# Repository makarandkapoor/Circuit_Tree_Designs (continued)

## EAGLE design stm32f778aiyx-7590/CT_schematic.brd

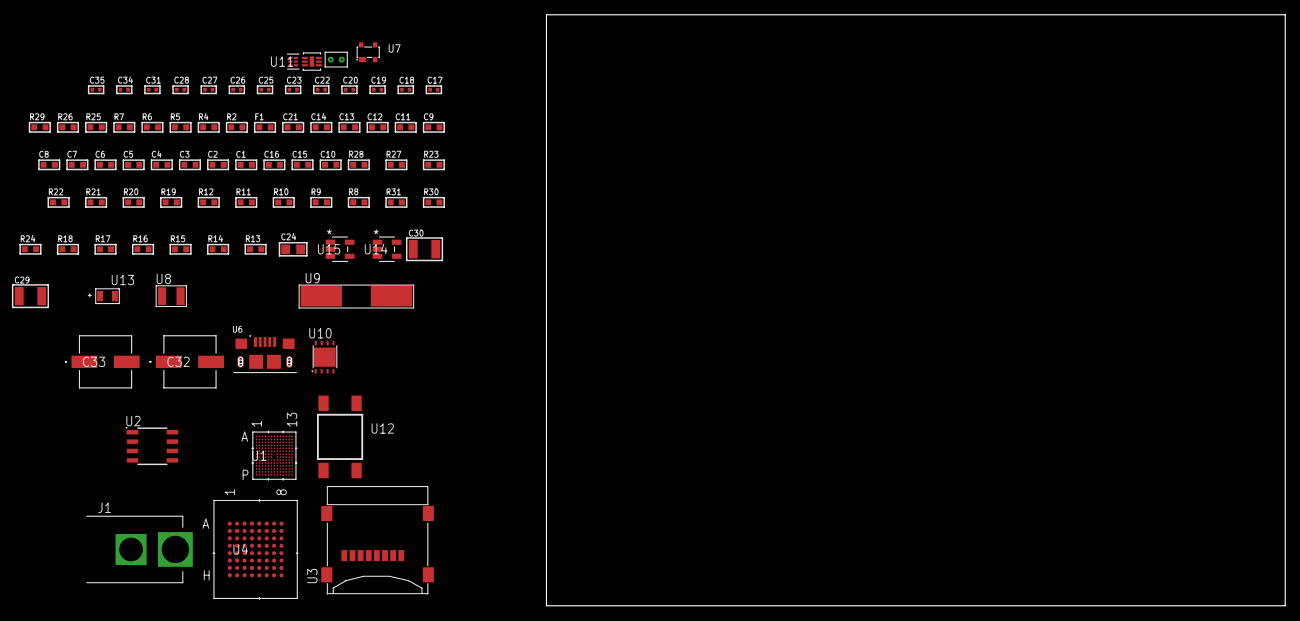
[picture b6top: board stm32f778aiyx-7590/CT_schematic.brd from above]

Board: 2 copper layers, 82 parts (0 on the bottom side), 86 nets, no tracks yet.

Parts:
C1, C13, C21: 1e-06; C0603
C2, C3, C4, C5, C6, C7, C8, C9, C11, C14: 1e-07; C0603
C10: 4.7e-06; C0603
C12: 1e-08; C0603
C15, C16: 2.2e-06; C0603
C17, C18, C19, C20: 1e-11; C0402
C22, C25, C26, C28, C34, C35: 1e-08; C0402
C23, C27, C31: 1e-07; C0402
C24: 1e-05; C0805
C29, C30: 1e-05; C1210
C32, C33: 0.0001; EXV-9H
F1: 240.0; L0603
J1: PJ-037B; PJ-037B_PACKAGE
R2, R26: 1000.0; R0603
R4, R5: 4700.0; R0603
R6, R7: 2200.0; R0603
R8, R9, R10, R11, R12, R19, R20, R21, R22, R23, R27, R28: 10000.0; R0603
R13, R14, R15, R16, R17, R18, R24: 100000.0; R0603
R25: 2231.0; R0603
R29: 9100.0; R0603
R30: 680000.0; R0603
R31: 120000.0; R0603
U1: STM32F778AIY6TR; WLCSP180
U2: AT25128B-SSHL-T; SOIC-8
U3: 0472192001; MOLEX_47219-2001
U4: mt28ew256aba1HPC-0SIT; LBGA-64
U5: SI7006-A20-IM; DFN-6
U6: 10118193-0001LF; FCI_10118193-0001LF
U7: prtr5v0u2ax; SOT143B
U8: ABS07-32.768KHZ-7-T
U9: ABLS-25.000MHZ-B2F-T
U10: LP3878SDX-ADJ/NOPB; WSON-8
U11: TPS3895ADRYR; SON-6
U12: 4-1437565-2; SW_4-1437565-2
U13: Q65110A2395; LGM67K-G1J2-24-Z
U14, U15: nc7sz125m5x; NC7SZ125M5X
U16: Dummy; DUMMY_PACKAGE_192

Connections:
CLK_CRYSTAL_U1_E12: C17.1, U1.E12, U8.1
CLK_CRYSTAL_U1_E13: C18.1, U1.E13, U8.2
CLK_CRYSTAL_U1_K12: C19.1, U1.K12, U9.1
CLK_CRYSTAL_U1_K13: C20.1, U1.K13, U9.2
GND: C1.2, C2.2, C3.2, C4.2, C5.2, C6.2, C7.2, C8.2, C9.2, C10.2, C11.2, C12.2, C13.2, C14.2, C15.2, C16.2, C17.2, C18.2, C19.2, C20.2, C21.2, C22.2, C23.2, C24.2, C25.2, C26.2, C27.2, C28.2, C29.2, C30.2, C31.2, C32.2, C33.2, C34.2, C35.2, J1.2, R2.2, R8.2, R26.2, R29.2, R31.2, U1.A8, U1.A11, U1.B6, U1.C2, U1.E3, U1.F1, U1.F13, U1.H5, U1.J9, U1.J13, U1.M1, U1.M11, U1.N4, U1.N5, U1.P9, U2.4, U3.6, U3.G1, U3.G2, U3.G3, U3.G4, U4.E8, U4.H2, U4.H7, U5.2, U5.7, U6.5, U6.6, U6.7, U6.8, U6.9, U7.1, U10.3, U10.PAD, U11.2, U13.C, U14.1, U14.3, U15.1, U15.3, U16.1
NET_U1_A10: R8.1, U1.A10
NET_U1_B9: R6.1, U1.B9, U5.6
NET_U1_C1: C16.1, U1.C1
NET_U1_C8: R7.1, U1.C8, U5.1
NET_U1_C10: R9.1, U1.C10
NET_U1_L11: R5.1, U1.L11, U15.4
NET_U1_M12: C12.1, C13.1, F1.1, U1.M12
NET_U1_P5: C15.1, U1.P5
NET_U1_P11: U12.3, U12.4
NET_U2_3: R10.1, U2.3
NET_U2_7: R12.1, U2.7
NET_U4_B4: R22.1, U4.B4
NET_U4_B5: R4.1, U4.B5, U14.4
NET_U10_1: C28.1, U10.1
NET_U10_6: R25.2, R26.1, U10.6
NET_U10_8: R24.1, U10.8
NET_U11_1: R28.1, R29.1, U11.1
NET_U11_3: R30.2, R31.1, U11.3
NET_U11_4: R27.1, U11.4, U14.2, U15.2
NET_U12_1: R2.1, U12.1, U12.2
PROC_DAC_OUT1: U1.L9, U16.2
PROC_FMC_A0: U1.G11, U4.E2
PROC_FMC_A1: U1.G12, U4.D2
PROC_FMC_A2: U1.G13, U4.C2
PROC_FMC_A3: U1.H11, U4.A2
PROC_FMC_A4: U1.H12, U4.B2
PROC_FMC_A5: U1.H13, U4.D3
PROC_FMC_A6: U1.K7, U4.C3
PROC_FMC_A7: U1.L8, U4.A3
PROC_FMC_A8: U1.K8, U4.B6
PROC_FMC_A9: U1.P8, U4.A6
PROC_FMC_A10: U1.N8, U4.C6
PROC_FMC_A11: U1.L7, U4.D6
PROC_FMC_A12: U1.H9, U4.B7
PROC_FMC_A13: U1.G9, U4.A7
PROC_FMC_A14: U1.G1, U4.C7
PROC_FMC_A15: U1.G2, U4.D7
PROC_FMC_A16: U1.K3, U4.E7
PROC_FMC_A17: U1.J4, U4.B3
PROC_FMC_A18: U1.L2, U4.C4
PROC_FMC_A19: U1.F10, U4.D5
PROC_FMC_A20: U1.C12, U4.D4
PROC_FMC_A21: U1.D12, U4.C5
PROC_FMC_A22: U1.E11, U4.B8
PROC_FMC_A23: U1.E10, U4.C8
PROC_FMC_D0: U1.L1, U4.E3
PROC_FMC_D1: U1.K2, U4.H3
PROC_FMC_D2: U1.A4, U4.E4
PROC_FMC_D3: U1.D5, U4.H4
PROC_FMC_D4: U1.M7, U4.H5
PROC_FMC_D5: U1.N7, U4.E5
PROC_FMC_D6: U1.P7, U4.H6
PROC_FMC_D7: U1.J6, U4.E6
PROC_FMC_D8: U1.K6, U4.F3
PROC_FMC_D9: U1.L6, U4.G3
PROC_FMC_D10: U1.P6, U4.F4
PROC_FMC_D11: U1.N6, U4.G4
PROC_FMC_D12: U1.M6, U4.F5
PROC_FMC_D13: U1.M3, U4.G6
PROC_FMC_D14: U1.L3, U4.F6
PROC_FMC_D15: U1.M2, U4.G7
PROC_FMC_NBL0: R23.1, U1.C9, U4.F7
PROC_FMC_NE2: R19.1, U1.D7, U4.F2
PROC_FMC_NOE: R20.1, U1.A5, U4.G2
PROC_FMC_NWAIT: U1.E6, U4.A4
PROC_FMC_NWE: R21.1, U1.C5, U4.A5
PROC_SDMMC1_CK: R14.1, U1.D4, U3.5
PROC_SDMMC1_CMD: R13.1, U1.D6, U3.3
PROC_SDMMC1_D0: R15.1, U1.G8, U3.7
PROC_SDMMC1_D1: R16.1, U1.E1, U3.8
PROC_SDMMC1_D2: R17.1, U1.B4, U3.1
PROC_SDMMC1_D3: R18.1, U1.C4, U3.2
PROC_SPI1_MISO: U1.C6, U2.2
PROC_SPI1_MOSI: U1.A9, U2.5
PROC_SPI1_NSS: R11.1, U1.A7, U2.1
PROC_SPI1_SCK: U1.B7, U2.6
PROC_USB_OTG_FS_DM: U1.E3, U6.2, U7.3
PROC_USB_OTG_FS_DP: U1.D1, U6.3, U7.2
PROC_USB_OTG_FS_VBUS: C21.1, U1.F4, U6.1, U7.4
VCC_S1_11V4: C29.1, C32.1, C33.1, J1.1, R24.2, U10.4
VCC_TIER1_3V3: C1.1, C2.1, C3.1, C4.1, C5.1, C6.1, C7.1, C8.1, C9.1, C10.1, C11.1, C14.1, C22.1, C23.1, C24.1, C25.1, C26.1, C27.1, C30.1, C31.1, C34.1, C35.1, F1.2, R4.2, R5.2, R6.2, R7.2, R9.2, R10.2, R11.2, R12.2, R13.2, R14.2, R15.2, R16.2, R17.2, R18.2, R19.2, R20.2, R21.2, R22.2, R23.2, R25.1, R27.2, R28.2, R30.1, U1.A6, U1.B2, U1.B8, U1.B11, U1.C13, U1.F2, U1.F12, U1.J12, U1.K1, U1.K9, U1.M8, U1.P4, U2.8, U3.4, U4.D8, U4.F1, U4.G5, U5.5, U10.5, U11.6, U14.5, U15.5

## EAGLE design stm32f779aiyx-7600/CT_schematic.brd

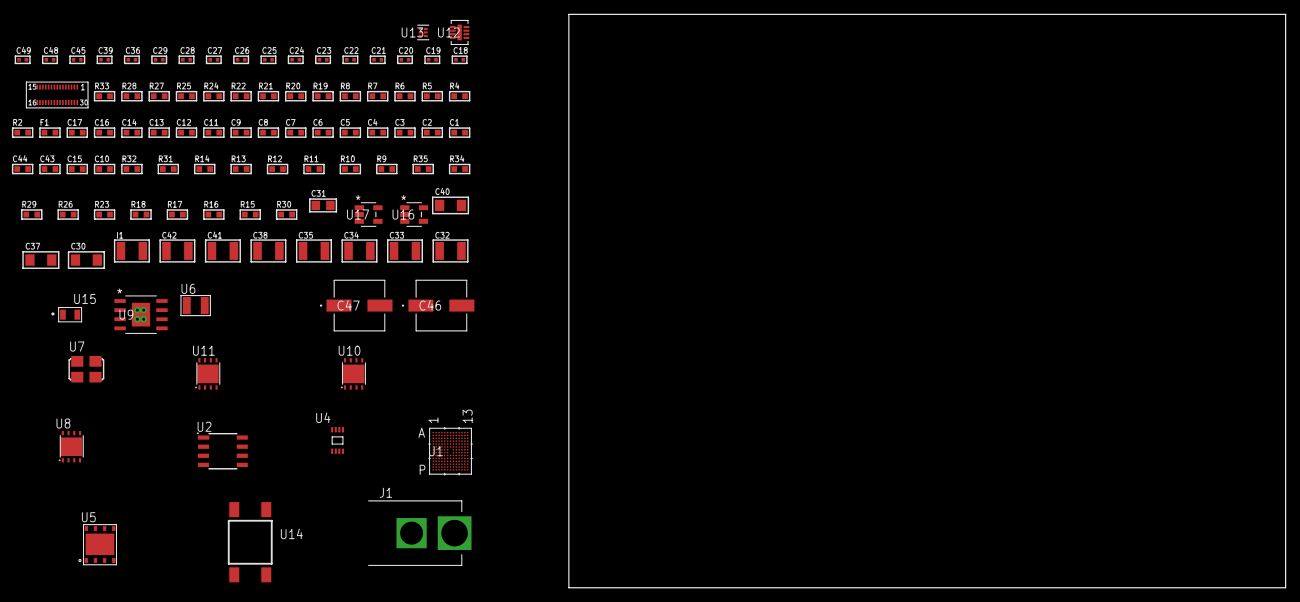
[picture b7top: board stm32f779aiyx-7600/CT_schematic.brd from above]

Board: 2 copper layers, 100.0 x 80.0 mm, 102 parts (0 on the bottom side), 57 nets, no tracks yet.

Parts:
C1, C13: 1e-06; C0603
C2, C3, C4, C5, C6, C7, C8, C9, C11, C14, C16, C17: 1e-07; C0603
C10: 4.7e-06; C0603
C12: 1e-08; C0603
C15, C43: 2.2e-06; C0603
C18, C19: 1e-11; C0402
C20, C26, C28, C29, C36, C39, C48, C49: 1e-08; C0402
C21, C22, C23, C24, C25, C27, C45: 1e-07; C0402
C30, C37, C40: 1e-05; C1206
C31: 1e-05; C0805
C32, C33, C34, C35, C38, C41, C42: 1e-05; C1210
C44: 2.2e-07; C0603
C46, C47: 0.0001; EXV-9H
F1: 240.0; L0603
I1: 1e-05; L1210
J1: PJ-037B; PJ-037B_PACKAGE
R2, R20, R25, R28: 1000.0; R0603
R4, R5: 4700.0; R0603
R6, R7, R8, R22: 2200.0; R0603
R9, R10, R11, R12, R13, R14, R31, R32: 10000.0; R0603
R15, R16, R17, R18, R23, R26, R29: 100000.0; R0603
R19: 200.0; R0603
R21: 910.0; R0603
R24: 1800.0; R0603
R27: 2231.0; R0603
R30: 1600000.0; R0603
R33: 9100.0; R0603
R34: 680000.0; R0603
R35: 120000.0; R0603
U1: STM32F779AIY6TR; WLCSP180
U2: AT25160B-SSHL-T; SOIC-8
U3: LH430WV2-SD01
U4: 24AA02T-I/MNY; TDFN-8/6MM
U5: SST26VF032B-104I/MF; WFDN-8
U6: ABS07-32.768KHZ-7-T
U7: ASFL1-25MHZ-NCS; ASFL1
U8, U10, U11: LP3878SDX-ADJ/NOPB; WSON-8
U9: MIC5234YME; SOIC-8_EP
U12: LT3494AEDDB#TRMPBF; DFN-8_DDB
U13: TPS3895ADRYR; SON-6
U14: 4-1437565-2; SW_4-1437565-2
U15: Q65110A2395; LGM67K-G1J2-24-Z
U16, U17: nc7sz125m5x; NC7SZ125M5X

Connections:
CLK_CRYSTAL_U1_E12: C18.1, U1.E12, U6.1
CLK_CRYSTAL_U1_E13: C19.1, U1.E13, U6.2
CLK_U1_K12: U1.K12, U7.3
GND: C1.2, C2.2, C3.2, C4.2, C5.2, C6.2, C7.2, C8.2, C9.2, C10.2, C11.2, C12.2, C13.2, C14.2, C15.2, C16.2, C17.2, C18.2, C19.2, C20.2, C21.2, C22.2, C23.2, C24.2, C25.2, C26.2, C27.2, C28.2, C29.2, C30.2, C31.2, C32.2, C33.2, C34.2, C35.2, C36.2, C37.2, C38.2, C39.2, C40.2, C41.2, C42.2, C43.2, C44.2, C45.2, C46.2, C47.2, C48.2, C49.2, J1.2, R2.2, R9.2, R14.2, R20.2, R22.2, R25.2, R28.2, R33.2, R35.2, U1.A8, U1.A11, U1.B6, U1.C2, U1.F1, U1.F13, U1.H5, U1.J9, U1.J13, U1.M1, U1.M11, U1.N4, U1.N5, U1.P9, U2.4, U3.1, U3.6, U3.9, U3.12, U3.15, U3.17, U3.18, U3.19, U3.24, U3.27, U4.4, U4.7, U5.4, U5.9, U7.2, U8.3, U8.PAD, U9.7, U9.EPAD, U10.3, U10.PAD, U11.3, U11.PAD, U12.2, U12.9, U13.2, U15.C, U16.1, U16.3, U17.1, U17.3
NET_U1_A10: R9.1, U1.A10
NET_U1_B9: R6.1, U1.B9, U4.6
NET_U1_C1: C17.1, U1.C1
NET_U1_C8: R7.1, U1.C8, U4.5
NET_U1_C10: R10.1, U1.C10
NET_U1_J3: C15.1, U1.H6, U1.J3
NET_U1_L11: R5.1, U1.L11, U17.4
NET_U1_M12: C12.1, C13.1, F1.1, U1.M12
NET_U1_P11: U14.3, U14.4
NET_U2_3: R11.1, U2.3
NET_U2_7: R13.1, U2.7
NET_U3_4: R4.1, U3.4, U16.4
NET_U3_20: R14.1, U3.20
NET_U8_1: C29.1, U8.1
NET_U8_6: R19.2, R20.1, U8.6
NET_U8_8: R18.1, U8.8
NET_U9_4: R21.2, R22.1, U9.4
NET_U10_1: C36.1, U10.1
NET_U10_6: R24.2, R25.1, U10.6
NET_U10_8: R23.1, U10.8
NET_U11_1: C39.1, U11.1
NET_U11_6: R27.2, R28.1, U11.6
NET_U11_8: R26.1, U11.8
NET_U12_1: I1.1, U12.1
NET_U12_5: R29.1, U12.5
NET_U12_6: R30.1, U12.6
NET_U12_8: C44.1, U12.8
NET_U13_1: R32.1, R33.1, U13.1
NET_U13_3: R34.2, R35.1, U13.3
NET_U13_4: R31.1, U13.4, U16.2, U17.2
NET_U14_1: R2.1, U14.1, U14.2
PROC_DSIHOST_CKN: U1.H3, U3.13
PROC_DSIHOST_CKP: U1.H4, U3.14
PROC_DSIHOST_D0N: U1.J2, U3.7
PROC_DSIHOST_D0P: U1.J1, U3.8
PROC_DSIHOST_D1N: U1.H2, U3.10
PROC_DSIHOST_D1P: U1.H1, U3.11
PROC_QUADSPI_BK1_IO0: U1.E1, U5.5
PROC_QUADSPI_BK1_IO1: U1.B4, U5.2
PROC_QUADSPI_BK1_IO2: R16.1, U1.E10, U5.3
PROC_QUADSPI_BK1_IO3: R17.1, U1.J11, U5.7
PROC_QUADSPI_BK1_NCS: R15.1, U1.K5, U5.1
PROC_QUADSPI_CLK: U1.J7, U5.6
PROC_SPI1_MISO: U1.C6, U2.2
PROC_SPI1_MOSI: U1.A9, U2.5
PROC_SPI1_NSS: R12.1, U1.A7, U2.1
PROC_SPI1_SCK: U1.B7, U2.6
VCC_S1_10V6: C30.1, C32.1, C33.1, C37.1, C40.1, C42.1, C46.1, C47.1, I1.2, J1.1, R18.2, R23.2, R26.2, R29.2, U8.4, U9.5, U9.8, U10.4, U11.4, U12.3, U12.4
VCC_TIER1_1V2: C16.1, C31.1, R19.1, U1.P5, U8.5
VCC_TIER1_1V5: C34.1, C35.1, R21.1, U3.29, U9.1
VCC_TIER1_2V8: C23.1, C24.1, C25.1, C38.1, R24.1, U3.16, U3.21, U3.22, U3.23, U10.5
VCC_TIER1_3V3: C1.1, C2.1, C3.1, C4.1, C5.1, C6.1, C7.1, C8.1, C9.1, C10.1, C11.1, C14.1, C20.1, C21.1, C26.1, C27.1, C28.1, C41.1, C45.1, C48.1, C49.1, F1.2, R4.2, R5.2, R6.2, R7.2, R8.2, R10.2, R11.2, R12.2, R13.2, R15.2, R16.2, R17.2, R27.1, R31.2, R32.2, R34.1, U1.A6, U1.B2, U1.B8, U1.B11, U1.C13, U1.F2, U1.F12, U1.J12, U1.K1, U1.K9, U1.M8, U1.P4, U2.8, U3.2, U4.8, U5.8, U7.4, U11.5, U13.6, U16.5, U17.5
VCC_TIER1_12V0: C22.1, C43.1, R30.2, U3.30, U12.7

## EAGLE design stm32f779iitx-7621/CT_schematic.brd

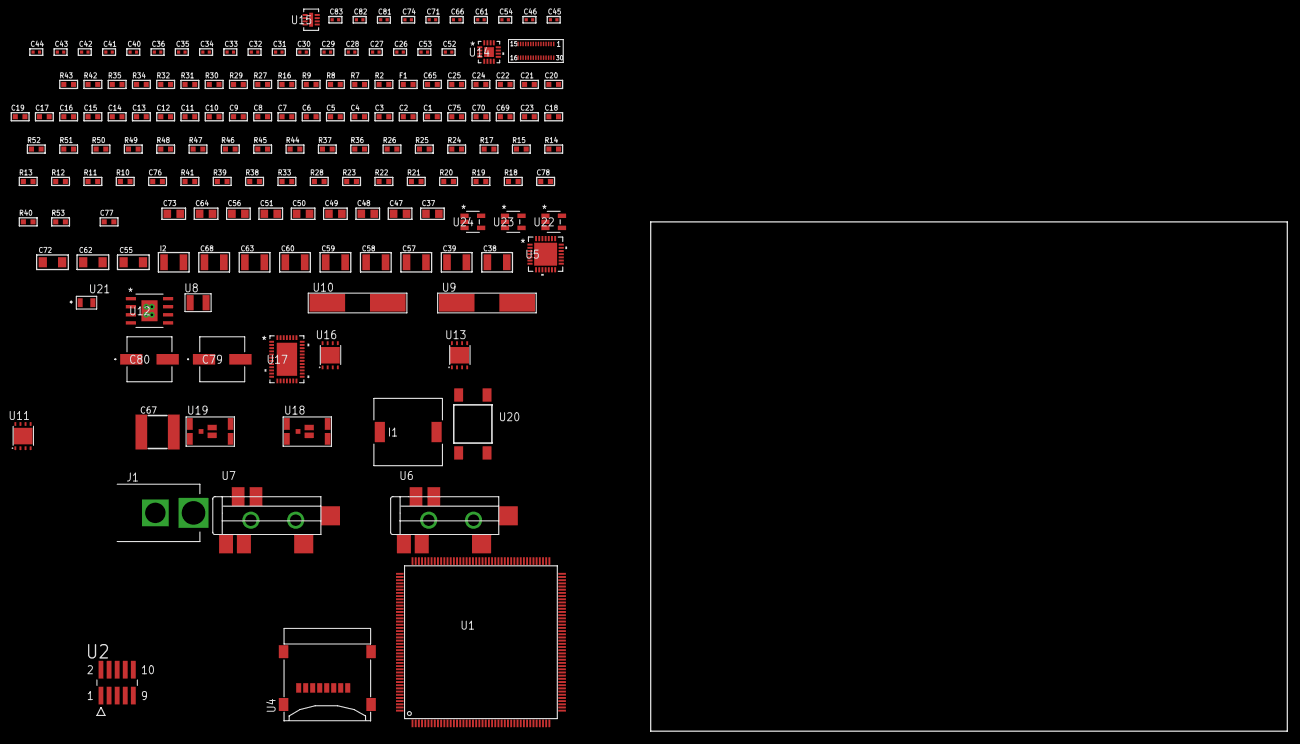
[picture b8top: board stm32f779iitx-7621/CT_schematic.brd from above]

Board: 2 copper layers, 100.0 x 80.0 mm, 159 parts (0 on the bottom side), 85 nets, no tracks yet.

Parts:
C1, C21, C65: 1e-06; C0603
C2, C3, C4, C5, C6, C7, C8, C9, C10, C11, C12, C13, C14, C15, C16, C17, C19, C22, C24, C25: 1e-07; C0603
C18: 4.7e-06; C0603
C20: 1e-08; C0603
C23, C69, C75: 2.2e-06; C0603
C26, C27, C28, C29: 1e-11; C0402
C30, C31, C32, C33, C34, C35, C36, C42, C43, C44, C45, C46, C66, C74: 1e-07; C0402
C37, C47, C48, C49, C50, C51, C56, C64, C73: 1e-05; C0805
C38, C39: 2.2e-05; C1210
C40, C41: 1e-09; C0402
C52, C53: 2.2e-11; C0402
C54, C61, C71, C81, C82, C83: 1e-08; C0402
C55, C62, C72: 1e-05; C1206
C57, C58, C59, C60, C63, C68: 1e-05; C1210
C67: 6.8e-05; 2220
C70: 2.2e-07; C0603
C76: 2.45e-08; R0603
C77: 2.8258362168397e-09; R0603
C78: 7.105e-09; R0603
C79, C80: 0.0001; EXV-9H
F1: 240.0; L0603
I1: 5.2e-06; DR1040
I2: 1e-05; L1210
J1: PJ-037B; PJ-037B_PACKAGE
R2, R30, R35, R43: 1000.0; R0603
R7, R8: 4700.0; R0603
R9, R32: 2200.0; R0603
R10, R11, R12, R13, R14, R15, R17, R44, R46, R47, R50, R51, R52: 10000.0; R0603
R16: 5.0; R0603
R18, R19, R20, R21, R22, R23, R28, R33, R39, R41: 100000.0; R0603
R24, R25, R26: 47000.0; R0603
R27: 680.0; R0603
R29, R42: 200.0; R0603
R31: 910.0; R0603
R34: 1800.0; R0603
R36: 20000.0; R0603
R37: 91000.0; R0603
R38: 300000.0; R0603
R40: 1600000.0; R0603
R45: 75000.0; R0603
R48, R49: 95300.0; R0603
R53: 83745.454545455; R0603
U1: STM32F779IIT6; LQFP176
U2: FTSH-105-01-L-DV-K; SAMTEC_FTSH-105-01-L-DV-K
U3: LH430WV2-SD01
U4: 0472192001; MOLEX_47219-2001
U5: WM8731CLSEFL; QFN-28
U6, U7: SJ-43515TS-SMT-TR
U8: ABS07-32.768KHZ-7-T
U9: ABLS-25.000MHZ-B2F-T
U10: ABLS-12.288MHZ-B4-T
U11, U13, U16: LP3878SDX-ADJ/NOPB; WSON-8
U12: MIC5234YME; SOIC-8_EP
U14: LTC3601EUD#PBF; QFN-16_EP
U15: LT3494AEDDB#TRMPBF; DFN-8_DDB
U17: LTC2928CUHF#PBF; QFN-38_UHF
U18, U19: IRF8306MTRPbF; IRF8306MTRPBF
U20: 4-1437565-2; SW_4-1437565-2
U21: Q65110A2395; LGM67K-G1J2-24-Z
U22, U23, U24: nc7sz125m5x; NC7SZ125M5X

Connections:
CLK_CRYSTAL_U1_9: C26.1, U1.9, U8.1
CLK_CRYSTAL_U1_10: C27.1, U1.10, U8.2
CLK_CRYSTAL_U1_29: C28.1, U1.29, U9.1
CLK_CRYSTAL_U1_30: C29.1, U1.30, U9.2
CLK_CRYSTAL_U5_1: C52.1, U5.1, U10.1
CLK_CRYSTAL_U5_2: C53.1, U5.2, U10.2
GND: C1.2, C2.2, C3.2, C4.2, C5.2, C6.2, C7.2, C8.2, C9.2, C10.2, C11.2, C12.2, C13.2, C14.2, C15.2, C16.2, C17.2, C18.2, C19.2, C20.2, C21.2, C22.2, C23.2, C24.2, C25.2, C26.2, C27.2, C28.2, C29.2, C30.2, C31.2, C32.2, C33.2, C34.2, C35.2, C36.2, C37.2, C41.2, C42.2, C43.2, C44.2, C45.2, C46.2, C47.2, C48.2, C49.2, C50.2, C51.2, C52.2, C53.2, C54.2, C55.2, C56.2, C57.2, C58.2, C59.2, C60.2, C61.2, C62.2, C63.2, C64.2, C65.2, C67.1, C67.2, C68.2, C69.2, C70.2, C71.2, C72.2, C73.2, C74.2, C75.2, C76.2, C77.2, C78.2, C79.2, C80.2, C81.2, C82.2, C83.2, J1.2, R2.2, R10.2, R16.2, R17.2, R24.2, R25.2, R26.2, R30.2, R32.2, R35.2, R36.2, R38.2, R43.2, R45.2, R48.2, R49.2, R50.2, R51.2, R52.2, U1.14, U1.22, U1.37, U1.61, U1.71, U1.95, U1.103, U1.109, U1.117, U1.130, U1.135, U1.148, U1.158, U2.3, U2.5, U3.1, U3.6, U3.9, U3.12, U3.15, U3.17, U3.18, U3.19, U3.24, U3.27, U4.6, U4.G1, U4.G2, U4.G3, U4.G4, U5.4, U5.15, U5.19, U5.25, U5.26, U5.29, U6.1, U7.1, U11.3, U11.PAD, U12.7, U12.EPAD, U13.3, U13.PAD, U14.1, U14.9, U14.17, U15.2, U15.9, U16.3, U16.PAD, U17.8, U17.9, U17.10, U17.12, U17.13, U17.24, U17.25, U17.30, U17.32, U17.39, U21.C, U22.2, U22.3, U23.1, U23.3, U24.1, U24.3
NET_U1_31: R8.1, U1.31, U24.4
NET_U1_39: C20.1, C21.1, F1.1, U1.38, U1.39
NET_U1_48: R12.1, U1.48
NET_U1_106: C23.1, U1.100, U1.106
NET_U1_129: C25.1, U1.129
NET_U1_166: R10.1, U1.166
NET_U1_171: R11.1, U1.171
NET_U1_176: U20.3, U20.4
NET_U2_9: R16.1, U2.9
NET_U3_4: R7.1, U3.4, U23.4
NET_U3_20: R17.1, U3.20
NET_U5_20: C46.1, C51.1, U5.20
NET_U6_2: C39.1, R25.1, U6.2
NET_U6_5: C38.1, R24.1, U6.5
NET_U7_5: C40.1, C41.1, R26.1, R27.1, U7.5
NET_U11_1: C54.1, U11.1
NET_U11_6: R29.2, R30.1, U11.6
NET_U11_8: R28.1, U11.8
NET_U12_4: R31.2, R32.1, U12.4
NET_U13_1: C61.1, U13.1
NET_U13_6: R34.2, R35.1, U13.6
NET_U13_8: R33.1, U13.8
NET_U14_3: C66.2, I1.1, U14.3, U14.4
NET_U14_6: C66.1, U14.6
NET_U14_7: C65.1, U14.7, U14.12
NET_U14_10: R38.1, U14.10
NET_U14_11: R36.1, R37.1, U14.11
NET_U14_ATNET_3: I1.2, R37.2
NET_U15_1: I2.1, U15.1
NET_U15_5: R39.1, U15.5
NET_U15_6: R40.1, U15.6
NET_U15_8: C70.1, U15.8
NET_U16_1: C71.1, U16.1
NET_U16_6: R42.2, R43.1, U16.6
NET_U16_8: R41.1, U16.8
NET_U17_3: R51.1, U17.3
NET_U17_6: R48.1, U17.6
NET_U17_7: R49.1, U17.7
NET_U17_16: R50.1, R53.1, U17.16
NET_U17_18: R47.1, U17.18
NET_U17_19: R46.1, U17.19, U17.20
NET_U17_21: R44.1, R45.1, U17.21, U22.4, U23.2, U24.2
NET_U17_22: C74.1, R44.2, R46.2, R47.2, U17.11, U17.22
NET_U17_26: C77.1, U17.26
NET_U17_27: C76.1, U17.27
NET_U17_28: C78.1, U17.28
NET_U17_38: R52.1, U17.38
NET_U18_3: U17.2, U18.3
NET_U19_3: U17.37, U19.3
NET_U20_1: R2.1, U20.1, U20.2
PROC_DSIHOST_CKN: U1.105, U3.13
PROC_DSIHOST_CKP: U1.104, U3.14
PROC_DSIHOST_D0N: U1.102, U3.7
PROC_DSIHOST_D0P: U1.101, U3.8
PROC_DSIHOST_D1N: U1.108, U3.10
PROC_DSIHOST_D1P: U1.107, U3.11
PROC_I2S1_CK: U1.51, U5.7
PROC_I2S1_SD: U1.53, U5.8
PROC_I2S1_WS: U1.50, U5.9, U5.11
PROC_SDMMC1_CK: R19.1, U1.141, U4.5
PROC_SDMMC1_CMD: R18.1, U1.144, U4.3
PROC_SDMMC1_D0: R20.1, U1.121, U4.7
PROC_SDMMC1_D1: R21.1, U1.122, U4.8
PROC_SDMMC1_D2: R22.1, U1.139, U4.1
PROC_SDMMC1_D3: R23.1, U1.140, U4.2
PROC_SYS_JTCK_SWCLK: R14.1, U1.137, U2.4
PROC_SYS_JTDO_SWO: U1.161, U2.6
PROC_SYS_JTMS_SWDIO: R15.1, U1.128, U2.2
RST_OUT_U2_JTAG_RST_B: R13.1, U2.10, U22.1
VCC_10V5: C75.1, C79.1, C80.1, J1.1, R53.2, U17.23, U18.1, U18.2, U18.6, U18.7, U19.1, U19.2, U19.6, U19.7
VCC_S1_10V5: C55.1, C57.1, C58.1, C62.1, C64.1, C68.1, I2.2, R28.2, R33.2, R39.2, U11.4, U12.5, U12.8, U13.4, U14.15, U14.16, U15.3, U15.4, U18.4, U18.5
VCC_S2_10V5: C72.1, R41.2, U16.4, U19.4, U19.5
VCC_TIER1_1V2: C24.1, C56.1, R29.1, U1.81, U11.5
VCC_TIER1_1V5: C59.1, C60.1, R31.1, U3.29, U12.1
VCC_TIER1_2V8: C33.1, C34.1, C35.1, C63.1, R34.1, U3.16, U3.21, U3.22, U3.23, U13.5
VCC_TIER1_3V3: C1.1, C2.1, C3.1, C4.1, C5.1, C6.1, C7.1, C8.1, C9.1, C10.1, C11.1, C12.1, C13.1, C14.1, C15.1, C16.1, C17.1, C18.1, C19.1, C22.1, C30.1, C31.1, C36.1, C37.1, C42.1, C43.1, C44.1, C45.1, C47.1, C48.1, C49.1, C50.1, C67.2, C81.1, C82.1, C83.1, F1.2, I1.2, R7.2, R8.2, R9.2, R11.2, R12.2, R13.2, R14.2, R15.2, R18.2, R19.2, R20.2, R21.2, R22.2, R23.2, R37.2, U1.6, U1.15, U1.23, U1.36, U1.49, U1.62, U1.72, U1.82, U1.96, U1.99, U1.118, U1.131, U1.136, U1.149, U1.159, U1.172, U2.1, U3.2, U4.4, U5.3, U5.5, U5.12, U5.18, U14.8, U22.5, U23.5, U24.5
VCC_TIER1_12V0: C32.1, C69.1, R40.2, U3.30, U15.7
VCC_TIER2_1V2: C73.1, R42.1, U16.5
